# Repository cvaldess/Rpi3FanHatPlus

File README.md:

# Rpi3FanHatPlus

Raspberry Pi 5 **HAT+** that drives the three fans of a case with a Microchip **EMC2303**
fan controller and breaks out the Pi's UART and a PPS input for a **GNSS module** (J2).

> **Status:** revision 1, not yet manufactured or tested.

## Features

- **EMC2303** I²C fan controller on the Pi's I²C1 bus (address `0x2E`, `ALERT` on GPIO5).
- **Fan 1 / Fan 2 (J5, J6):** standard 4-pin PWM fans with tachometer, e.g. Noctua NF-A4x10 PWM (12 V).
- **Fan 3 (J4):** small 2-wire 12 V fan (up to 100 mA) that cools the GNSS module, switched on
  the low side by an AO3400A MOSFET with an SS14 flyback diode.
- **GNSS connector (J2):** connects a GNSS module (a Unicore UM982 in this build) to the
  Raspberry Pi: UART0 (GPIO14/15), PPS on GPIO18, 5 V and GND.
- **12 V input (J3)** for the fans, protected by a 0.5 A resettable fuse.
- HAT+ ID EEPROM (AT24CS64) as required by the HAT+ specification.
- 4-layer board, 65 × 56.5 mm HAT+ outline, M3 mounting holes. Designed to sit on top of a PoE HAT.

## Connectors

| Ref | Function | Pinout |
|-----|----------|--------|
| J1 | Raspberry Pi 40-pin GPIO (Samtec HLE-120-02-F-DV-BE-A, bottom-entry SMT socket) | Standard Raspberry Pi header |
| J2 | **GNSS module to Raspberry Pi** (2×6, 2.54 mm, right angle) | 1: PPS → GPIO18 · 3: +5 V · 5: GPIO14 TXD (Pi → GNSS RX) · 7: GPIO15 RXD (GNSS TX → Pi) · 9: GND · others not connected |
| J3 | 12 V input (1×2, 2.54 mm) | 1: +12 V · 2: GND — **not keyed, check polarity** |
| J4 | Fan 3, 2-wire (1×2, 2.54 mm) | 1: +12 V · 2: Fan − (switched) |
| J5, J6 | Fan 1, Fan 2, 4-pin PWM (Molex 47053) | 1: GND · 2: +12 V · 3: Tach · 4: PWM |

GNSS signals on J2 are 3.3 V logic: the module's UART and PPS must not exceed 3.3 V.

## Raspberry Pi resources

| Signal | GPIO | Notes |
|--------|------|-------|
| I²C SDA / SCL | GPIO2 / GPIO3 | EMC2303 at `0x2E` |
| Fan controller ALERT | GPIO5 | Active low, 4.7 kΩ pull-up |
| UART TXD / RXD | GPIO14 / GPIO15 | GNSS module (J2) |
| GNSS PPS | GPIO18 | |
| HAT+ ID EEPROM | GPIO0 / GPIO1 | |

Example `config.txt` lines:

```text
dtparam=i2c_arm=on
enable_uart=1
dtoverlay=pps-gpio,gpiopin=18
```

### Fan controller notes

- PWM1/PWM2 reach the 4-pin fans through non-inverting 2N7002 stages: the EMC2303's default
  PWM polarity and open-drain output are correct.
- The fans stop at 0 % duty. At power-up the EMC2303 watchdog drives all fans to full speed
  after 4 s until the host writes a fan setting.
- Fan 3 has no tachometer: run it in direct-drive mode (no RPM control loop).

## Manufacturing

The [`HATPlus/fab/`](HATPlus/fab/) folder contains:

- `Rpi3FanHatPlus-gerbers.zip`: Gerber (4 copper layers, masks, paste, silkscreen, outline) and Excellon drill files.
- `HAT+-BOM-PCBWay.csv`: bill of materials with manufacturer part numbers and LCSC codes.
- `HAT+-CPL-PCBWay.csv`: component placement file, in millimetres, top side only.

The files are prepared for PCB fabrication and assembly (PCBA) at
[PCBWay](https://www.pcbway.com/). Board: 4 layers, 1.6 mm, ENIG recommended,
minimum track/space 0.15 mm, minimum drill 0.4 mm.

## Design files and tools

[KiCad 10](https://www.kicad.org/) project in [`HATPlus/`](HATPlus/) (`HAT+.kicad_pro`); project
footprint libraries in `HATPlus/libs/` and `libs/`.

The schematic review, design changes, footprints and fabrication outputs were done with
[Konnect](https://github.com/Orchis-ai-LLC/Konnect-EDA), an AI-assisted PCB design tool for
KiCad 10, driven by Anthropic's Claude through [Claude Code](https://claude.com/claude-code).

## Credits

Based on the [Raspberry Pi HAT+ KiCad template](https://github.com/MisterHW/RPi5-HATplus)
by Helge Wurst (CERN-OHL-S v2).

## License

Copyright © 2024 Helge Wurst (HAT+ template), © 2026 CValdesS.

This source describes Open Hardware and is licensed under the CERN-OHL-S v2
([LICENSE](LICENSE)). You may redistribute and modify this source and make products using it
under the terms of the CERN-OHL-S v2. This source is distributed WITHOUT ANY EXPRESS OR IMPLIED
WARRANTY, INCLUDING OF MERCHANTABILITY, SATISFACTORY QUALITY AND FITNESS FOR A PARTICULAR
PURPOSE. Please see the CERN-OHL-S v2 for applicable conditions.

Source location: https://github.com/cvaldess/Rpi3FanHatPlus

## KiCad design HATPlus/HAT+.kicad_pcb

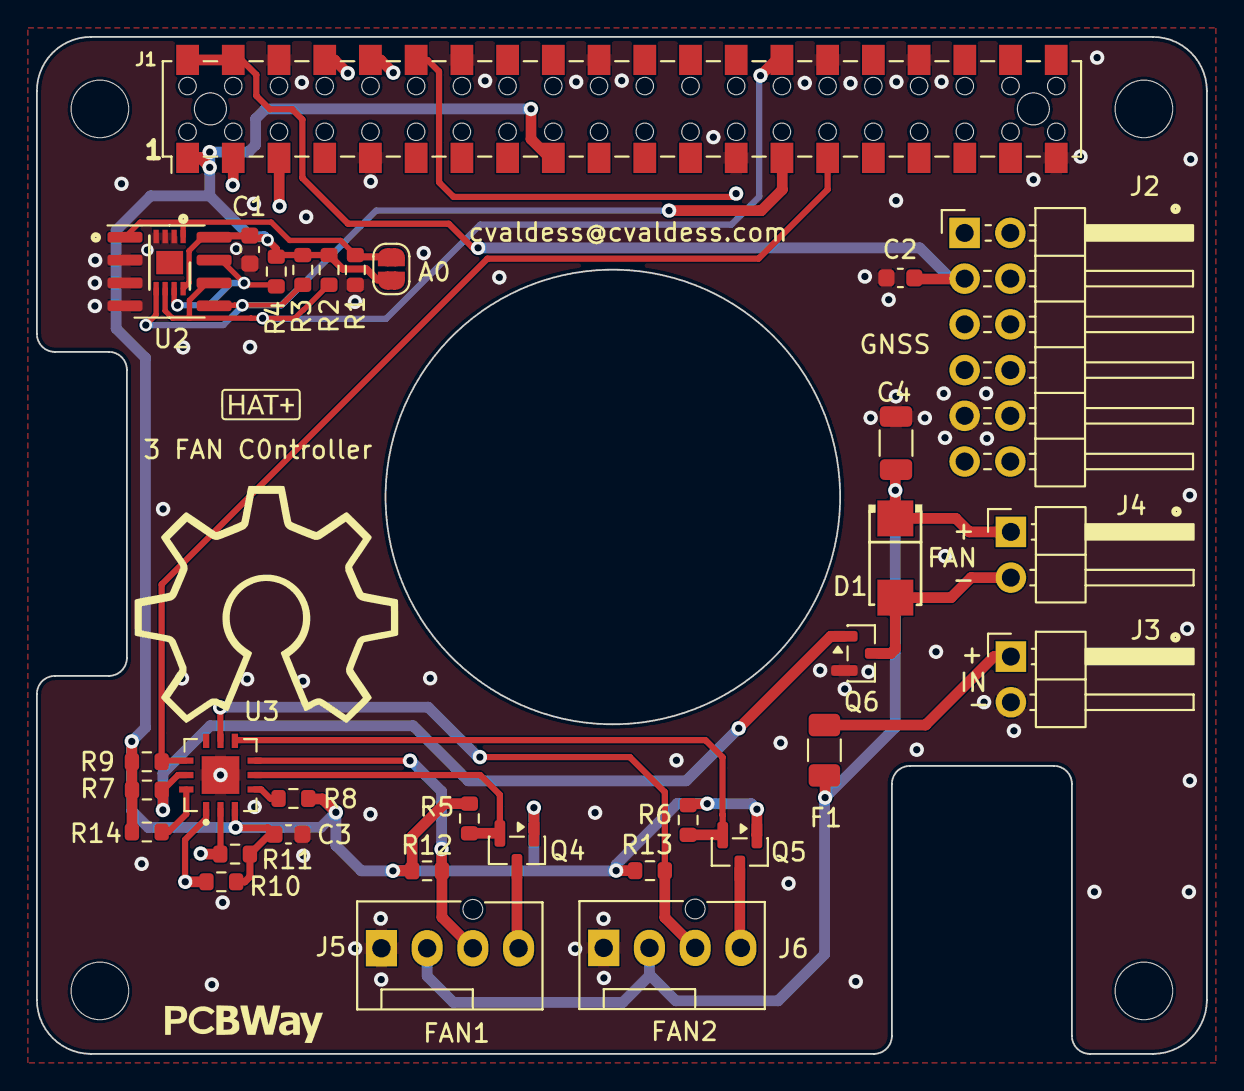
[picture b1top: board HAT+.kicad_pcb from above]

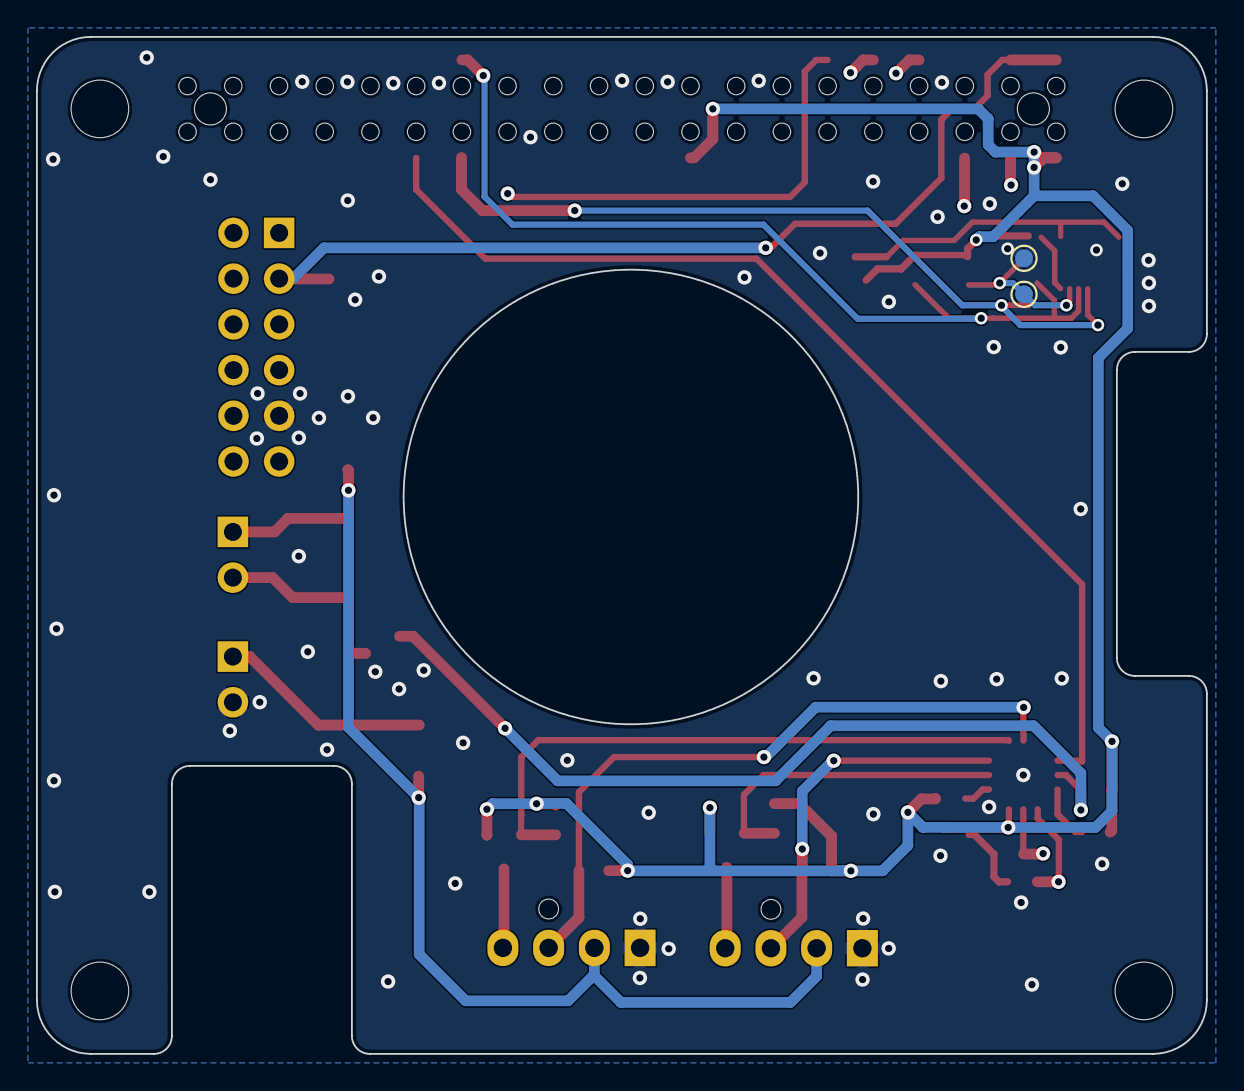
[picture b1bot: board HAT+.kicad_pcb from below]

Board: 4 copper layers, 65.0 x 56.5 mm, 39 parts (2 on the bottom side), 25 nets.

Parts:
A0: SolderJumper_2_Open; SolderJumper-2_P1.3mm_Open_RoundedPad1.0x1.5mm
C1, C2, C3: 100n 50V; C_0603_1608Metric
C4: 10u 50V; C_1206_3216Metric
D1: SS14; SMA_L4.3-W2.6-LS5.1-RD
F1: 0.5A; Fuse_1206_3216Metric
GND1: TestPoint_Alt; TestPoint_Pad_D1.0mm
H1, H2, H3, H4: MountingHole 3.2mm; MountingHole_3.2mm_M3_DIN965
J1: RPi_40Pin; Samtec_HLE-120-02-xxx-DV-BE-A_2x20_P2.54mm_Horizontal_Rever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
J2: GNSS; PinHeader_2x06_P2.54mm_Horizontal
J3: 12V; PinHeader_1x02_P2.54mm_Horizontal
J4: Fan3; PinHeader_1x02_P2.54mm_Horizontal
J5: FAN1; FanPinHeader_1x04_P2.54mm_Vertical
J6: FAN2; FanPinHeader_1x04_P2.54mm_Vertical
Q4, Q5: 2N7002; SOT-23
Q6: AO3400A; SOT-23
R1, R2, R3, R4: 3.9k; R_0603_1608Metric
R5, R6, R7, R8, R9, R10, R11: 4.7K; R_0603_1608Metric
R12, R13: 2.2K; R_0603_1608Metric
R14: 10K; R_0603_1608Metric
U1: AT24CS64-SSHM; SOIC-8_3.9x4.9mm_P1.27mm
U2: AT24CS64-MAHM; DFN-8-1EP_3x2mm_P0.5mm_EP1.3x1.5mm
U3: EMC2303-1-KP-TR; TQFN-12_L4.0-W4.0-P0.80-BL-EP2.1_PasteGrid
WP1: TestPoint_Alt; TestPoint_Pad_D1.0mm

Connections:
/Fan Controller/+3V3: A0.2 (B), C1.1, C3.1, J1.1, J1.17, Q4.1 (G), Q5.1 (G), R2.2, R3.2, R4.2, R5.1, R6.1, R7.1, R8.1, R9.1, R10.1, R11.1, R12.1, R13.1, R14.1, U1.8 (VCC), U2.8 (VCC), U3.3 (VDD)
/Fan Controller/+12V_BUS: F1.1, J3.1
/Fan Controller/+12V_FAN: C4.1, D1.1 (K), F1.2, J4.1, J5.2 (+), J6.2 (+)
/Fan Controller/ADDR_SEL: R8.2, U3.4 (ADDR_SEL)
/Fan Controller/ALERT: J1.29, R9.2, U3.10 (~ALERT)
/Fan Controller/FAN_DRV1: Q4.2 (S), R5.2, U3.5 (PWM1)
/Fan Controller/FAN_DRV2: Q5.2 (S), R6.2, U3.7 (PWM2)
/Fan Controller/FAN_DRV3: Q6.1 (G), R7.2, U3.11 (PWM3)
/Fan Controller/FAN_PWM1: J5.4 (PWM), Q4.3 (D)
/Fan Controller/FAN_PWM2: J6.4 (PWM), Q5.3 (D)
/Fan Controller/FAN_TACH1: J5.3 (Tacho), R12.2, U3.6 (TACH1)
/Fan Controller/FAN_TACH2: J6.3 (Tacho), R13.2, U3.8 (TACH2)
/Fan Controller/FAN_TACH3: R14.2, U3.12 (TACH3)
/Fan Controller/FAN_V-: D1.2 (A), J4.2, Q6.3 (D)
/Fan Controller/I2C_SCL: J1.5, R11.2, U3.2 (SMCLK)
/Fan Controller/I2C_SDA: J1.3, R10.2, U3.1 (SMDATA)
/GNSS/GPIO14_TXD: J1.8, J2.5
/GNSS/GPIO15_RXD: J1.10, J2.7
/GNSS/GPIO18_PCM_CLK: J1.12, J2.1
/GNSS/HAT_5V0: C2.1, J1.2, J1.4, J2.3
/HAT+/GPIO0_ID_SDA0: J1.27, R3.1, U1.5 (SDA), U2.5 (SDA)
/HAT+/GPIO1_ID_SCL0: J1.28, R2.1, U1.6 (SCL), U2.6 (SCL)
GND: C1.2, C2.2, C3.2, C4.2, GND1.1 (1_1), J1.6, J1.9, J1.14, J1.20, J1.25, J1.30, J1.34, J1.39, J2.9, J3.2, J5.1 (-), J6.1 (-), Q6.2 (S), R1.1, U1.2 (A1), U1.3 (A2), U1.4 (GND), U2.2 (A1), U2.3 (A2), U2.4 (GND), U3.13 (EP)
unnamed: A0.1 (A), R1.2, U1.1 (A0), U2.1 (A0)
unnamed: R4.1, U1.7 (WP), U2.7 (WP), WP1.1 (1_1)

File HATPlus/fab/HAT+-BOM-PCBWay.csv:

"Designator","Qty","Manufacturer","Mfg Part #","Description/Value","Package/Footprint","LCSC Part #"
"C1,C2,C3","3","Yageo","CC0603KRX7R9BB104","100n 50V","Capacitor_SMD:C_0603_1608Metric","C14663"
"C4","1","Samsung Electro-Mechanics","CL31A106KBHNNNE","10u 50V","Capacitor_SMD:C_1206_3216Metric","C13585"
"D1","1","MDD(Microdiode Semiconductor)","SS14","SS14","easyeda2kicad:SMA_L4.3-W2.6-LS5.1-RD","C2480"
"F1","1","JDTfuse","ASMD1206-050-30V","0.5A","Fuse:Fuse_1206_3216Metric","C2982267"
"J1","1","Samtec","HLE-120-02-F-DV-BE-A","RPi_40Pin","Connector_Samtec_Reverse:Samtec_HLE-120-02-xxx-DV-BE-A_2x20_P2.54mm_Horizontal_Reverse","C3319272"
"J2","1","XFCN","PZ254R-12-12P","GNSS","Connector_PinHeader_2.54mm:PinHeader_2x06_P2.54mm_Horizontal","C492434"
"J3","1","XFCN","PZ254R-11-02P","12V","Connector_PinHeader_2.54mm:PinHeader_1x02_P2.54mm_Horizontal","C492410"
"J4","1","XFCN","PZ254R-11-02P","Fan3","Connector_PinHeader_2.54mm:PinHeader_1x02_P2.54mm_Horizontal","C492410"
"J5","1","Molex","47053-1000","FAN1","Connector:FanPinHeader_1x04_P2.54mm_Vertical","C240840"
"J6","1","Molex","47053-1000","FAN2","Connector:FanPinHeader_1x04_P2.54mm_Vertical","C240840"
"Q4,Q5","2","JSCJ","2N7002","2N7002","Package_TO_SOT_SMD:SOT-23","C8545"
"Q6","1","Alpha & Omega Semicon","AO3400A","AO3400A","Package_TO_SOT_SMD:SOT-23","C20917"
"R1,R2,R3,R4","4","HWA CHN","HRC0603F3901ENTN","3.9k","Resistor_SMD:R_0603_1608Metric","C54920913"
"R5,R6,R7,R8,R9,R10,R11","7","HWA CHN","HRC0603F4701ENTN","4.7K","Resistor_SMD:R_0603_1608Metric","C54920925"
"R12,R13","2","HWA CHN","HRC0603F2201ENTN","2.2K","Resistor_SMD:R_0603_1608Metric","C54920892"
"R14","1","UNI-ROYAL(Uniroyal Elec)","0603WAF1002T5E","10K","Resistor_SMD:R_0603_1608Metric","C25804"
"U1","1","MICROCHIP","AT24CS64-SSHM-B","AT24CS64-SSHM","Package_SO:SOIC-8_3.9x4.9mm_P1.27mm","C615478"
"U3","1","MICROCHIP(美国微芯)","EMC2303-1-KP-TR","EMC2303-1-KP-TR","libs:TQFN-12_L4.0-W4.0-P0.80-BL-EP2.1_PasteGrid","C621414"
